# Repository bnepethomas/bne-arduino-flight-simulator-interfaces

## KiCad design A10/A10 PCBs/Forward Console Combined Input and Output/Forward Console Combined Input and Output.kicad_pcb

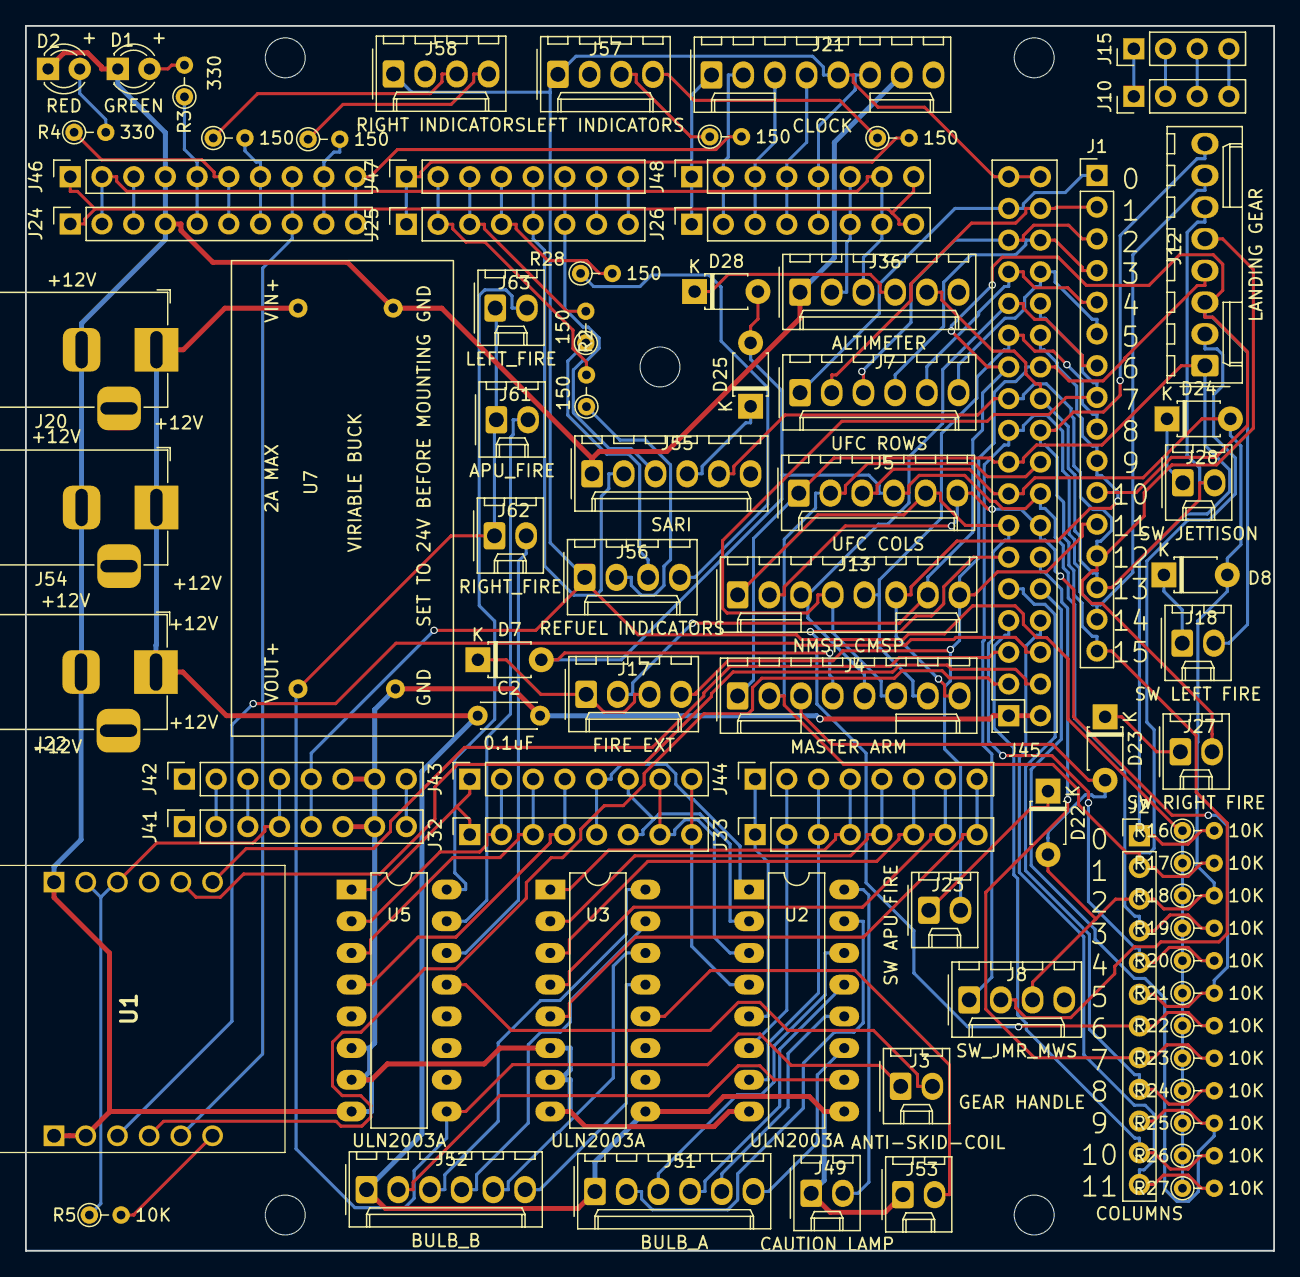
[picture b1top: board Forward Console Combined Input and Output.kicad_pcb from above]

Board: 2 copper layers, 100.0 x 98.1 mm, 87 parts (0 on the bottom side), 116 nets.

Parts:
C2: 0.1uF; C_Disc_D4.3mm_W1.9mm_P5.00mm
D1: GREEN; LED_D3.0mm
D2: RED; LED_D3.0mm
D7, D8, D22, D23, D24, D25, D28: D; D_T-1_P5.08mm_Horizontal
H1, H2, H3, H4: MountingHole; MountingHole_3.2mm
J1: ROWS; PinHeader_1x16_P2.54mm_Vertical
J2: COLUMNS; PinHeader_1x12_P2.54mm_Vertical
J3: GEAR HANDLE; Molex_KK-254_AE-6410-02A_1x02_P2.54mm_Vertical
J4: MASTER ARM; Molex_KK-254_AE-6410-08A_1x08_P2.54mm_Vertical
J5: UFC COLS; Molex_KK-254_AE-6410-06A_1x06_P2.54mm_Vertical
J7: UFC ROWS; Molex_KK-254_AE-6410-06A_1x06_P2.54mm_Vertical
J8: SW_JMR_MWS; Molex_KK-254_AE-6410-04A_1x04_P2.54mm_Vertical
J10, J15: PATCH; PinHeader_1x04_P2.54mm_Vertical
J12: LANDING GEAR; Molex_KK-254_AE-6410-08A_1x08_P2.54mm_Vertical
J13: NMSP CMSP; Molex_KK-254_AE-6410-08A_1x08_P2.54mm_Vertical
J17: FIRE EXT; Molex_KK-254_AE-6410-04A_1x04_P2.54mm_Vertical
J18: SW LEFT FIRE; Molex_KK-254_AE-6410-02A_1x02_P2.54mm_Vertical
J20: 12Vout; BarrelJack_Horizontal
J21: CLOCK; Molex_KK-254_AE-6410-08A_1x08_P2.54mm_Vertical
J22: 12VIN; BarrelJack_Horizontal
J23: SW APU FIRE; Molex_KK-254_AE-6410-02A_1x02_P2.54mm_Vertical
J24, J46: PWM; PinSocket_1x10_P2.54mm_Vertical
J25, J47: PWM; PinSocket_1x08_P2.54mm_Vertical
J26, J48: Communication; PinSocket_1x08_P2.54mm_Vertical
J27: SW RIGHT FIRE; Molex_KK-254_AE-6410-02A_1x02_P2.54mm_Vertical
J28: SW JETTISON; Molex_KK-254_AE-6410-02A_1x02_P2.54mm_Vertical
J32, J33, J43, J44: Analog; PinSocket_1x08_P2.54mm_Vertical
J36: ALTIMETER; Molex_KK-254_AE-6410-06A_1x06_P2.54mm_Vertical
J41, J42: Power; PinSocket_1x08_P2.54mm_Vertical
J45: Digital; PinSocket_2x18_P2.54mm_Vertical
J49: CAUTION LAMP; Molex_KK-254_AE-6410-02A_1x02_P2.54mm_Vertical
J51: BULB_A; Molex_KK-254_AE-6410-06A_1x06_P2.54mm_Vertical
J52: BULB_B; Molex_KK-254_AE-6410-06A_1x06_P2.54mm_Vertical
J53: ANTI-SKID-COIL; Molex_KK-254_AE-6410-02A_1x02_P2.54mm_Vertical
J54: 12VOUT; BarrelJack_Horizontal
J55: SARI; Molex_KK-254_AE-6410-06A_1x06_P2.54mm_Vertical
J56: REFUEL INDICATORS; Molex_KK-254_AE-6410-04A_1x04_P2.54mm_Vertical
J57: LEFT INDICATORS; Molex_KK-254_AE-6410-04A_1x04_P2.54mm_Vertical
J58: RIGHT INDICATORS; Molex_KK-254_AE-6410-04A_1x04_P2.54mm_Vertical
J61: APU_FIRE; Molex_KK-254_AE-6410-02A_1x02_P2.54mm_Vertical
J62: RIGHT_FIRE; Molex_KK-254_AE-6410-02A_1x02_P2.54mm_Vertical
J63: LEFT_FIRE; Molex_KK-254_AE-6410-02A_1x02_P2.54mm_Vertical
MH1: MountingHole_3.2mm
R1, R2, R28, R29, R30, R31, R32: 150; R_Axial_DIN0204_L3.6mm_D1.6mm_P2.54mm_Vertical
R3, R4: 330; R_Axial_DIN0204_L3.6mm_D1.6mm_P2.54mm_Vertical
R5, R16, R17, R18, R19, R20, R21, R22, R23, R24, R25, R26, R27: 10K; R_Axial_DIN0204_L3.6mm_D1.6mm_P2.54mm_Vertical
U1: USR-ES1; USRES1
U2, U3, U5: ULN2003A; DIP-16_W7.62mm_LongPads
U7: VIRIABLE BUCK; VARIABLE_BUCK

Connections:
+3V3: J41.4, J42.4, R5.1, U1.B2 (3V3_1), U1.B3 (3V3_2)
+5V: J21.5, J41.5, J42.5, J45.35, J45.36, J56.1, J57.1, J58.1, R16.1, R17.1, R18.1, R19.1, R20.1, R21.1, R22.1, R23.1, R24.1, R25.1, R26.1, R27.1
+12V: C2.1, J20.1, J22.1, J49.1, J51.1, J52.1, J53.1, J54.1, U2.9 (COM), U3.9 (COM), U7.1 (VIN)
+24V: J3.1, J61.1, J62.1, J63.1, U5.9 (COM), U7.4 (24V_OUT)
/*12: J24.6, J46.6, R4.1
/*13: J24.5, J46.5, R3.1
/AREF: J24.3, J46.3
/COIL AND LAMP DRIVERS/ANCHR: J52.4, U3.15 (O2)
/COIL AND LAMP DRIVERS/B_APU_FIRE: J61.2, U5.15 (O2)
/COIL AND LAMP DRIVERS/B_GEAR HANDLE: J3.2, U5.13 (O4)
/COIL AND LAMP DRIVERS/B_LEFT_FIRE: J63.2, U5.16 (O1)
/COIL AND LAMP DRIVERS/B_RIGHT_FIRE: J62.2, U5.14 (O3)
/COIL AND LAMP DRIVERS/CAUTION_LAMP-: J49.2, U2.16 (O1)
/COIL AND LAMP DRIVERS/COIL_ANTI_SKID: J53.2, U3.12 (O5)
/COIL AND LAMP DRIVERS/EGI: J51.6, U2.11 (O6)
/COIL AND LAMP DRIVERS/HARS: J51.5, U2.12 (O5)
/COIL AND LAMP DRIVERS/ILS: J52.6, U3.13 (O4)
/COIL AND LAMP DRIVERS/MISSLE LAUNCH: J51.4, U2.13 (O4)
/COIL AND LAMP DRIVERS/PRI: J51.2, U2.15 (O2)
/COIL AND LAMP DRIVERS/SEP: J51.3, U2.14 (O3)
/COIL AND LAMP DRIVERS/STR PT: J52.3, U3.16 (O1)
/COIL AND LAMP DRIVERS/TCN: J52.5, U3.14 (O3)
/COIL AND LAMP DRIVERS/TISL: J52.2, U2.10 (O7)
/IOREF: J41.2, J42.2
/~RESET: J41.3, J42.3
A0 D54: J32.1, J43.1, U5.1 (I1)
A1 D55: J32.2, J43.2, U5.2 (I2)
A2 D56: J32.3, J43.3, U5.3 (I3)
A3 D57: J32.4, J43.4, U5.4 (I4)
A4 D58: J32.5, J43.5, U2.1 (I1)
A5 D59: J32.6, J43.6, U2.2 (I2)
A6 D60: J32.7, J43.7, U2.3 (I3)
A7 D61: J32.8, J43.8, U2.4 (I4)
A8 D62: J33.1, J44.1, U2.5 (I5)
A9 D63: J33.2, J44.2, U2.6 (I6)
A10 D64: J33.3, J44.3, U2.7 (I7)
A11 D65: J33.4, J44.4, U3.1 (I1)
A12 D66: J33.5, J44.5, U3.2 (I2)
A13 D67: J33.6, J44.6, U3.3 (I3)
A14 D68: J33.7, J44.7, U3.4 (I4)
A15 D69: J33.8, J44.8, U3.5 (I5)
D0: J25.8, J47.8
D1: J25.7, J47.7
D2: J25.6, J47.6, J55.3
D3: J25.5, J47.5, J55.2
D4: J25.4, J47.4, R28.2
D5: J25.3, J47.3, R2.2
D6: J25.2, J47.2, R1.2
D7: J25.1, J47.1, R30.2
D8: J24.10, J46.10, R29.2
D9: J24.9, J46.9, R32.2
D11: J24.7, J46.7, R31.2
D14: J21.1, J26.1, J48.1
D15: J21.2, J26.2, J48.2
D16: J21.3, J26.3, J48.3
D17: J21.4, J26.4, J48.4
D18: J21.6, J26.5, J48.5
D19: J26.6, J36.2, J48.6
D20 SDA: J24.2, J26.7, J36.3, J46.2, J48.7
D21 SCL: J24.1, J26.8, J46.1, J48.8
D22: J1.1, J7.1, J45.33
D23: J1.2, J7.2, J45.34
D24: J1.3, J7.3, J45.31
D25: J1.4, J7.4, J45.32
D26: J1.5, J7.5, J45.29
D27: J1.6, J7.6, J45.30
D28: J1.7, J4.5, J13.3, J45.27
D29: J1.8, J4.6, J13.4, J45.28
D30: J1.9, J4.7, J13.5, J45.25
D31: J1.10, J4.8, J13.6, J45.26
D32: J1.11, J12.3, J13.7, J17.2, J18.2, J45.23
D33: J1.12, J12.4, J13.8, J17.4, J23.2, J45.24
D34: J1.13, J12.5, J27.2, J45.21, J55.5
D35: J1.14, J12.6, J28.2, J36.5, J45.22
D36: J1.15, J8.1, J12.7, J45.19
D37: J1.16, J8.2, J12.8, J45.20
D38: J2.1, J4.1, J5.1, J12.1, J45.17, R16.2
D39: J2.2, J4.2, J5.2, J12.2, J45.18, R17.2
D40: D8.2 (A), D22.2 (A), D23.2 (A), D24.2 (A), J2.3, J4.3, J5.3, J8.3, J45.15, R18.2
D41: D7.2 (A), D25.2 (A), D28.2 (A), J2.4, J4.4, J5.4, J45.16, R19.2
D42: J2.5, J5.5, J13.1, J45.13, R20.2
D43: J2.6, J5.6, J13.2, J45.14, R21.2
D44: J2.7, J45.11, R22.2
D45: J2.8, J45.12, R23.2
D46: J2.9, J45.9, R24.2
D47: J2.10, J45.10, R25.2
D48: J2.11, J45.7, R26.2
D49: J2.12, J45.8, R27.2
ES1_RST: J45.4, U1.B5 (RST)
GND: C2.2, D1.1 (K), D2.1 (K), J20.2, J21.7, J22.2, J24.4, J36.1, J41.6, J41.7, J42.6, J42.7, J45.1, J45.2, J46.4, J54.2, J55.1, U1.A1 (GND_1), U1.A2 (GND_2), U1.B1 (GND_3), U2.8 (GND), U3.6 (I6), U3.7 (I7), U3.8 (GND), U5.6 (I6), U5.7 (I7), U5.8 (GND), U7.2 (GND), U7.3 (GND)
MISO: J45.5, U1.B6 (MISO)
MOSI: J45.6, U1.A3 (MOSI)
unnamed: D1.2 (A), R3.2
unnamed: D2.2 (A), R4.2
unnamed: D7.1 (K), J17.1, J17.3
unnamed: D8.1 (K), J18.1
unnamed: D22.1 (K), J23.1
unnamed: D23.1 (K), J27.1
unnamed: D24.1 (K), J28.1
unnamed: D25.1 (K), J55.4
unnamed: D28.1 (K), J36.4
unnamed: J10.1, J15.1
unnamed: J10.2, J15.2
unnamed: J10.3, J15.3
unnamed: J10.4, J15.4
unnamed: J56.2, R1.1
unnamed: J56.3, R2.1
unnamed: J56.4, R28.1
unnamed: J57.3, R29.1
unnamed: J57.4, R30.1
unnamed: J58.3, R31.1
unnamed: J58.4, R32.1
unnamed: R5.2, U1.A6 (INT)
SCLK: J45.3, U1.A4 (SCLK)
SS: J24.8, J46.8, U1.A5 (CS)
VCC: J41.8, J42.8

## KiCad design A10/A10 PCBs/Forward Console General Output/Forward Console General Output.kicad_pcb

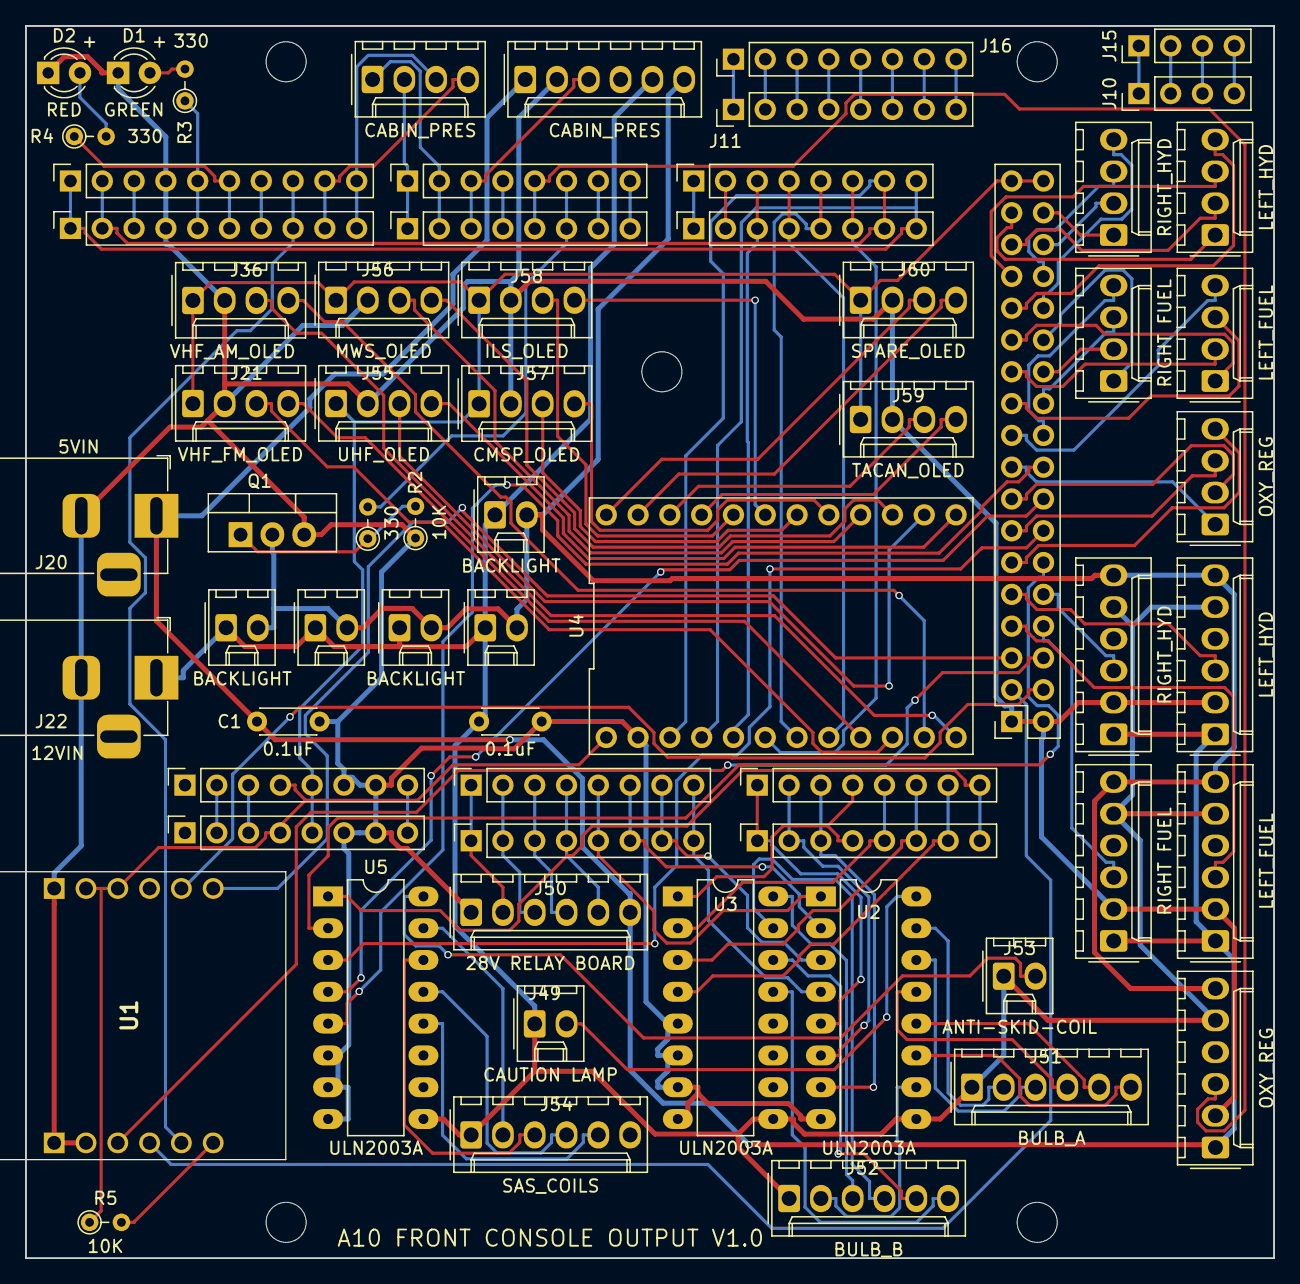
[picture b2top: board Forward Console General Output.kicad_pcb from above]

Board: 2 copper layers, 99.7 x 98.4 mm, 70 parts (0 on the bottom side), 128 nets.

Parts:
C1, C2: 0.1uF; C_Disc_D4.3mm_W1.9mm_P5.00mm
D1: GREEN; LED_D3.0mm
D2: RED; LED_D3.0mm
H1, H2, H3, H4: MountingHole; MountingHole_3.2mm
J3, J6, J9, J14, J19: BACKLIGHT; Molex_KK-254_AE-6410-02A_1x02_P2.54mm_Vertical
J10, J15: PATCH; PinHeader_1x04_P2.54mm_Vertical
J11, J16: PATCH; PinHeader_1x08_P2.54mm_Vertical
J20: 5VIN; BarrelJack_Horizontal
J21: VHF_FM_OLED; Molex_KK-254_AE-6410-04A_1x04_P2.54mm_Vertical
J22: 12VIN; BarrelJack_Horizontal
J23: CABIN_PRES; Molex_KK-254_AE-6410-06A_1x06_P2.54mm_Vertical
J24, J46: PWM; PinSocket_1x10_P2.54mm_Vertical
J25, J47: PWM; PinSocket_1x08_P2.54mm_Vertical
J26, J48: Communication; PinSocket_1x08_P2.54mm_Vertical
J27: OXY_REG; Molex_KK-254_AE-6410-06A_1x06_P2.54mm_Vertical
J28: RIGHT FUEL; Molex_KK-254_AE-6410-06A_1x06_P2.54mm_Vertical
J29: LEFT_FUEL; Molex_KK-254_AE-6410-06A_1x06_P2.54mm_Vertical
J30: RIGHT_HYD; Molex_KK-254_AE-6410-06A_1x06_P2.54mm_Vertical
J31: LEFT_HYD; Molex_KK-254_AE-6410-06A_1x06_P2.54mm_Vertical
J32, J33, J43, J44: Analog; PinSocket_1x08_P2.54mm_Vertical
J34: CABIN_PRES; Molex_KK-254_AE-6410-04A_1x04_P2.54mm_Vertical
J35: OXY_REG; Molex_KK-254_AE-6410-04A_1x04_P2.54mm_Vertical
J36: VHF_AM_OLED; Molex_KK-254_AE-6410-04A_1x04_P2.54mm_Vertical
J37: RIGHT_HYD; Molex_KK-254_AE-6410-04A_1x04_P2.54mm_Vertical
J38: LEFT_FUEL; Molex_KK-254_AE-6410-04A_1x04_P2.54mm_Vertical
J39: RIGHT FUEL; Molex_KK-254_AE-6410-04A_1x04_P2.54mm_Vertical
J40: LEFT_HYD; Molex_KK-254_AE-6410-04A_1x04_P2.54mm_Vertical
J41, J42: Power; PinSocket_1x08_P2.54mm_Vertical
J45: Digital; PinSocket_2x18_P2.54mm_Vertical
J49: CAUTION LAMP; Molex_KK-254_AE-6410-02A_1x02_P2.54mm_Vertical
J50: 28V RELAY BOARD; Molex_KK-254_AE-6410-06A_1x06_P2.54mm_Vertical
J51: BULB_A; Molex_KK-254_AE-6410-06A_1x06_P2.54mm_Vertical
J52: BULB_B; Molex_KK-254_AE-6410-06A_1x06_P2.54mm_Vertical
J53: ANTI-SKID-COIL; Molex_KK-254_AE-6410-02A_1x02_P2.54mm_Vertical
J54: SAS_COILS; Molex_KK-254_AE-6410-06A_1x06_P2.54mm_Vertical
J55: UHF_OLED; Molex_KK-254_AE-6410-04A_1x04_P2.54mm_Vertical
J56: MWS_OLED; Molex_KK-254_AE-6410-04A_1x04_P2.54mm_Vertical
J57: CMSP_OLED; Molex_KK-254_AE-6410-04A_1x04_P2.54mm_Vertical
J58: ILS_OLED; Molex_KK-254_AE-6410-04A_1x04_P2.54mm_Vertical
J59: TACAN_OLED; Molex_KK-254_AE-6410-04A_1x04_P2.54mm_Vertical
J60: SPARE_OLED; Molex_KK-254_AE-6410-04A_1x04_P2.54mm_Vertical
MH1: MountingHole_3.2mm
Q1: IRF1405PBF; TO-220-3_Vertical
R1, R3, R4: 330; R_Axial_DIN0204_L3.6mm_D1.6mm_P2.54mm_Vertical
R2, R5: 10K; R_Axial_DIN0204_L3.6mm_D1.6mm_P2.54mm_Vertical
U1: USR-ES1; USRES1
U2, U3, U5: ULN2003A; DIP-16_W7.62mm_LongPads
U4: TCA9548APWR; DIP-24_TCA9548A

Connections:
+3V3: J41.4, J42.4, R5.1, U1.B2 (3V3_1), U1.B3 (3V3_2), U4.1 (VCC)
+5V: J21.1, J36.1, J41.5, J42.5, J45.35, J45.36, J55.1, J56.1, J57.1, J58.1, J59.1, J60.1
+5VD: C1.1, J20.1, J23.1, J27.1, J28.1, J29.1, J30.1, J31.1, J50.6
+12V: C2.1, J3.1, J6.1, J9.1, J14.1, J19.1, J22.1, J23.5, J27.5, J28.5, J29.5, J30.5, J31.5, J49.1, J51.1, J52.1, J53.1, J54.1, U2.9 (COM), U3.9 (COM), U5.9 (COM)
/22: J40.1, J45.33
/23: J37.1, J45.34
/24: J40.2, J45.31
/25: J37.2, J45.32
/26: J40.3, J45.29
/27: J37.3, J45.30
/28: J40.4, J45.27
/29: J37.4, J45.28
/30: J38.1, J45.25
/31: J39.1, J45.26
/32: J38.2, J45.23
/33: J39.2, J45.24
/34: J38.3, J45.21
/35: J39.3, J45.22
/36: J38.4, J45.19
/37: J39.4, J45.20
/38: J35.1, J45.17
/40: J35.2, J45.15
/42: J35.3, J45.13
/47: J30.3, J45.10
/48: J29.3, J45.7
/49: J28.3, J45.8
/*2: J25.6, J47.6, R1.2
/*3: J25.5, J27.3, J47.5
/*4: J25.4, J47.4
/*5: J23.3, J25.3, J47.3
/*6: J25.2, J34.1, J47.2
/*7: J25.1, J34.2, J47.1
/*8: J24.10, J34.3, J46.10
/*9: J24.9, J34.4, J46.9
/*11: J24.7, J46.7
/*12: J24.6, J46.6, R4.1
/*13: J24.5, J46.5, R3.1
/*44: J35.4, J45.11
/*46: J31.3, J45.9
/A0: J32.1, J43.1, J50.2
/A1: J32.2, J43.2, J50.3
/A2: J32.3, J43.3, J50.4
/A3: J32.4, J43.4, J50.5
/AREF: J24.3, J46.3
/BACKLIGHT_-V: J3.2, J6.2, J9.2, J14.2, J19.2, J23.6, J27.6, J28.6, J29.6, J30.6, J31.6, Q1.2 (D)
/COIL AND LAMP DRIVERS/ANCHR: J52.4, U3.15 (O2)
/COIL AND LAMP DRIVERS/CAUTION_LAMP-: J49.2, U2.16 (O1)
/COIL AND LAMP DRIVERS/COIL_ANTI_SKID: J53.2, U5.16 (O1)
/COIL AND LAMP DRIVERS/COIL_L_PITCH: J54.4, U5.13 (O4)
/COIL AND LAMP DRIVERS/COIL_L_YAW: J54.2, U5.15 (O2)
/COIL AND LAMP DRIVERS/COIL_R_PITCH: J54.5, U5.12 (O5)
/COIL AND LAMP DRIVERS/COIL_R_YAW: J54.3, U5.14 (O3)
/COIL AND LAMP DRIVERS/EGI: J51.6, U2.11 (O6)
/COIL AND LAMP DRIVERS/HARS: J51.5, U2.12 (O5)
/COIL AND LAMP DRIVERS/ILS: J52.6, U3.13 (O4)
/COIL AND LAMP DRIVERS/MISSLE LAUNCH: J51.4, U2.13 (O4)
/COIL AND LAMP DRIVERS/PRI: J51.2, U2.15 (O2)
/COIL AND LAMP DRIVERS/SEP: J51.3, U2.14 (O3)
/COIL AND LAMP DRIVERS/STR PT: J52.3, U3.16 (O1)
/COIL AND LAMP DRIVERS/TCN: J52.5, U3.14 (O3)
/COIL AND LAMP DRIVERS/TISL: J52.2, U2.10 (O7)
/I2C_SEL_A0: J26.4, J48.4, U4.8 (A2)
/I2C_SEL_A1: J26.5, J48.5, U4.7 (A1)
/I2C_SEL_A2: J26.6, J48.6, U4.6 (A0)
/I2C_SEL_RESET: J26.3, J48.3, U4.5 (~RESET)
/IOREF: J41.2, J42.2
/RX0/0: J25.8, J47.8
/RX3/15: J26.2, J48.2
/SC0: J21.3, U4.10 (SC0)
/SC1: J36.3, U4.12 (SC1)
/SC2: J55.3, U4.14 (SC2)
/SC3: J56.3, U4.16 (SC3)
/SC4: J57.3, U4.18 (SC4)
/SC5: J58.3, U4.20 (SC5)
/SC6: J59.3, U4.22 (SC6)
/SC7: J60.3, U4.24 (SC7)
/SCL: J24.1, J26.8, J46.1, J48.8, U4.4 (SCL)
/SD0: J21.4, U4.9 (SD0)
/SD1: J36.4, U4.11 (SD1)
/SD2: J55.4, U4.13 (SD2)
/SD3: J56.4, U4.15 (SD3)
/SD4: J57.4, U4.17 (SD4)
/SD5: J58.4, U4.19 (SD5)
/SD6: J59.4, U4.21 (SD6)
/SD7: J60.4, U4.23 (SD7)
/SDA: J24.2, J26.7, J46.2, J48.7, U4.3 (SDA)
/TX0/1: J25.7, J47.7
/TX3/14: J26.1, J48.1
/~RESET: J41.3, J42.3
ES1_RST: J45.4, U1.B5 (RST)
GND: C1.2, C2.2, D1.1 (K), D2.1 (K), J20.2, J21.2, J22.2, J23.2, J24.4, J27.2, J28.2, J29.2, J30.2, J31.2, J36.2, J41.6, J41.7, J42.6, J42.7, J45.1, J45.2, J46.4, J50.1, J55.2, J56.2, J57.2, J58.2, J59.2, J60.2, Q1.3 (S), R2.1, U1.A1 (GND_1), U1.A2 (GND_2), U1.B1 (GND_3), U2.8 (GND), U3.5 (I5), U3.6 (I6), U3.7 (I7), U3.8 (GND), U4.2 (GND), U5.6 (I6), U5.7 (I7), U5.8 (GND)
MISO: J45.5, U1.B6 (MISO)
MOSI: J45.6, U1.A3 (MOSI)
unnamed: D1.2 (A), R3.2
unnamed: D2.2 (A), R4.2
unnamed: J10.1, J15.1
unnamed: J10.2, J15.2
unnamed: J10.3, J15.3
unnamed: J10.4, J15.4
unnamed: J11.1, J16.1
unnamed: J11.2, J16.2
unnamed: J11.3, J16.3
unnamed: J11.4, J16.4
unnamed: J11.5, J16.5
unnamed: J11.6, J16.6
unnamed: J11.7, J16.7
unnamed: J11.8, J16.8
unnamed: Q1.1 (G), R1.1, R2.2
unnamed: R5.2, U1.A6 (INT)
O_ANCHR_LAMP: J33.5, J44.5, U3.2 (I2)
O_ANTI_SKID: J33.8, J44.8, U5.1 (I1)
O_CAUTION_LAMP-: J32.5, J43.5, U2.1 (I1)
O_COIL_L_PITCH: J45.16, U5.4 (I4)
O_COIL_L_YAW: J45.12, U5.2 (I2)
O_COIL_R_PITCH: J45.18, U5.5 (I5)
O_COIL_R_YAW: J45.14, U5.3 (I3)
O_EGI_LAMP: J33.2, J44.2, U2.6 (I6)
O_HARS_LAMP: J33.1, J44.1, U2.5 (I5)
O_ILS_LAMP: J33.7, J44.7, U3.4 (I4)
O_MISSILE_LAMP: J32.8, J43.8, U2.4 (I4)
O_PRI_LAMP: J32.6, J43.6, U2.2 (I2)
O_SEP_LAMP: J32.7, J43.7, U2.3 (I3)
O_STR_PT_LAMP: J33.4, J44.4, U3.1 (I1)
O_TCN_LAMP: J33.6, J44.6, U3.3 (I3)
O_TISL_LAMP: J33.3, J44.3, U2.7 (I7)
SCLK: J45.3, U1.A4 (SCLK)
SS: J24.8, J46.8, U1.A5 (CS)
VCC: J41.8, J42.8

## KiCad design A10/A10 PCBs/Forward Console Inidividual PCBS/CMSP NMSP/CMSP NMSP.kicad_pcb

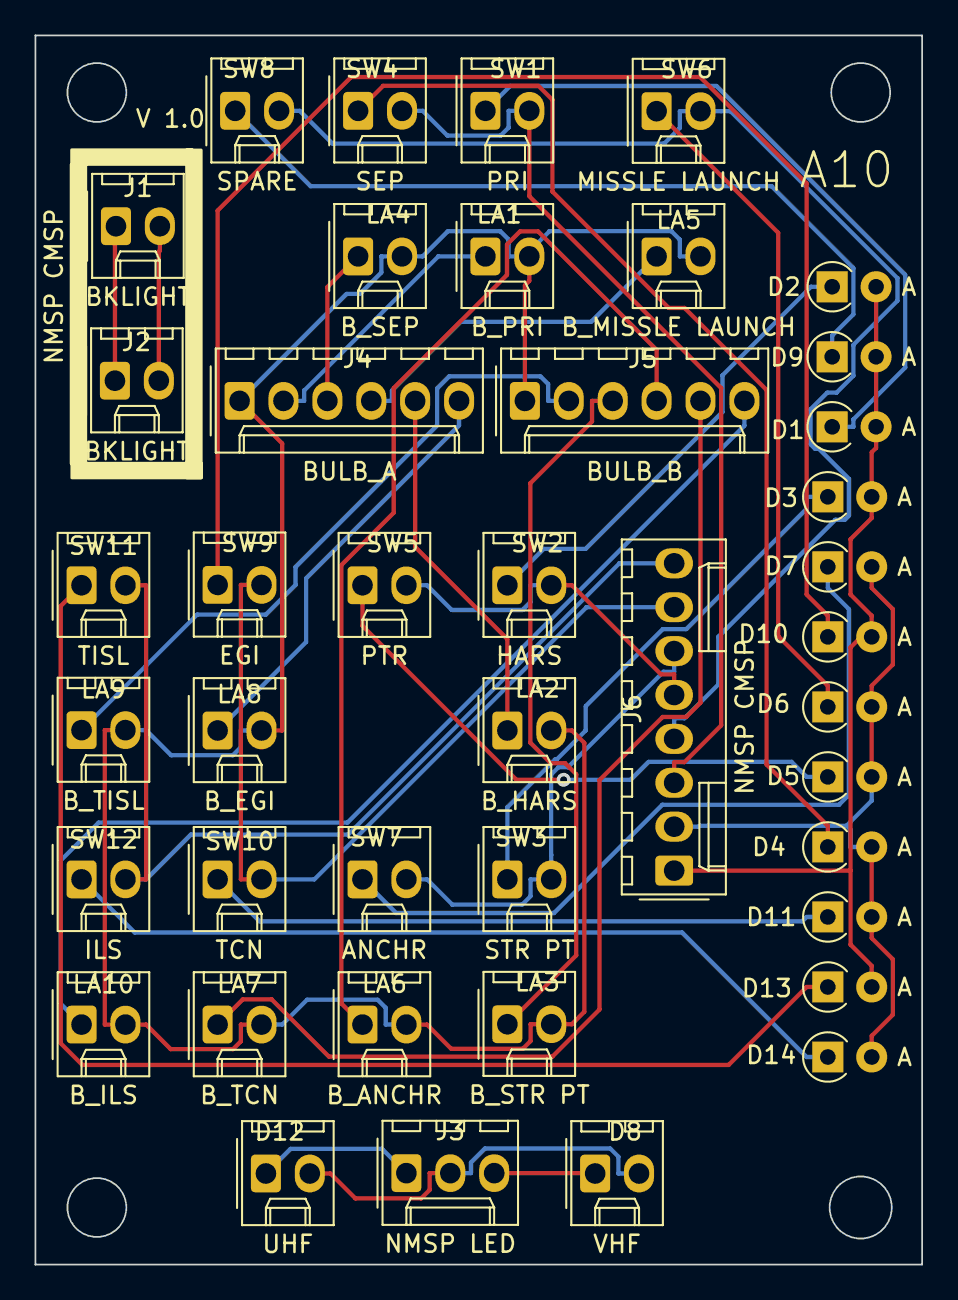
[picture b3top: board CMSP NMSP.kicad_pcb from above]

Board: 2 copper layers, 51.3 x 71.1 mm, 42 parts (0 on the bottom side), 36 nets.

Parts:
D1, D2, D3, D4, D5, D6, D7, D9, D10, D11, D13, D14: D; D_A-405_P2.54mm_Vertical_AnodeUp
D8: VHF; Molex_KK-254_AE-6410-02A_1x02_P2.54mm_Vertical
D12: UHF; Molex_KK-254_AE-6410-02A_1x02_P2.54mm_Vertical
J1, J2: BKLIGHT; Molex_KK-254_AE-6410-02A_1x02_P2.54mm_Vertical
J3: NMSP LED; Molex_KK-254_AE-6410-03A_1x03_P2.54mm_Vertical
J4: BULB_A; Molex_KK-254_AE-6410-06A_1x06_P2.54mm_Vertical
J5: BULB_B; Molex_KK-254_AE-6410-06A_1x06_P2.54mm_Vertical
J6: NMSP CMSP; Molex_KK-254_AE-6410-08A_1x08_P2.54mm_Vertical
LA1: B_PRI; Molex_KK-254_AE-6410-02A_1x02_P2.54mm_Vertical
LA2: B_HARS; Molex_KK-254_AE-6410-02A_1x02_P2.54mm_Vertical
LA3: B_STR PT; Molex_KK-254_AE-6410-02A_1x02_P2.54mm_Vertical
LA4: B_SEP; Molex_KK-254_AE-6410-02A_1x02_P2.54mm_Vertical
LA5: B_MISSLE LAUNCH; Molex_KK-254_AE-6410-02A_1x02_P2.54mm_Vertical
LA6: B_ANCHR; Molex_KK-254_AE-6410-02A_1x02_P2.54mm_Vertical
LA7: B_TCN; Molex_KK-254_AE-6410-02A_1x02_P2.54mm_Vertical
LA8: B_EGI; Molex_KK-254_AE-6410-02A_1x02_P2.54mm_Vertical
LA9: B_TISL; Molex_KK-254_AE-6410-02A_1x02_P2.54mm_Vertical
LA10: B_ILS; Molex_KK-254_AE-6410-02A_1x02_P2.54mm_Vertical
SW1: PRI; Molex_KK-254_AE-6410-02A_1x02_P2.54mm_Vertical
SW2: HARS; Molex_KK-254_AE-6410-02A_1x02_P2.54mm_Vertical
SW3: STR PT; Molex_KK-254_AE-6410-02A_1x02_P2.54mm_Vertical
SW4: SEP; Molex_KK-254_AE-6410-02A_1x02_P2.54mm_Vertical
SW5: PTR; Molex_KK-254_AE-6410-02A_1x02_P2.54mm_Vertical
SW6: MISSLE LAUNCH; Molex_KK-254_AE-6410-02A_1x02_P2.54mm_Vertical
SW7: ANCHR; Molex_KK-254_AE-6410-02A_1x02_P2.54mm_Vertical
SW8: SPARE; Molex_KK-254_AE-6410-02A_1x02_P2.54mm_Vertical
SW9: EGI; Molex_KK-254_AE-6410-02A_1x02_P2.54mm_Vertical
SW10: TCN; Molex_KK-254_AE-6410-02A_1x02_P2.54mm_Vertical
SW11: TISL; Molex_KK-254_AE-6410-02A_1x02_P2.54mm_Vertical
SW12: ILS; Molex_KK-254_AE-6410-02A_1x02_P2.54mm_Vertical

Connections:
/+12V: J4.1, J5.1, LA1.2 (+), LA2.2 (+), LA3.2 (+), LA4.2 (+), LA5.2 (+), LA6.2 (+), LA7.2 (+), LA8.2 (+), LA9.2 (+), LA10.2 (+)
/ANCHR: J5.4, LA6.1 (-)
/COL4: D1.2 (A), D2.2 (A), D3.2 (A), D9.2 (A), D10.2 (A), D13.2 (A), J6.1
/COL5: D4.2 (A), D5.2 (A), D6.2 (A), D7.2 (A), D11.2 (A), D14.2 (A), J6.2
/EGI: J4.6, LA8.1 (-)
/HARS: J4.5, LA2.1 (-)
/ILS: J5.6, LA10.1 (-)
/MISSLE LAUNCH: J4.4, LA5.1 (-)
/PRI: J4.2, LA1.1 (-)
/ROW6: J6.3, SW1.2, SW4.2
/ROW7: J6.4, SW6.2, SW8.2
/ROW8: J6.5, SW2.2, SW5.2 (B)
/ROW9: J6.6, SW3.2, SW7.2
/ROW10: J6.7, SW9.2, SW10.2
/ROW11: J6.8, SW11.2, SW12.2
/SEP: J4.3, LA4.1 (-)
/STR PT: J5.3, LA3.1 (-)
/TCN: J5.5, LA7.1 (-)
/TISL: J5.2, LA9.1 (-)
unnamed: D1.1 (K), SW1.1
unnamed: D2.1 (K), SW2.1
unnamed: D3.1 (K), SW3.1
unnamed: D4.1 (K), SW4.1
unnamed: D5.1 (K), SW5.1 (A)
unnamed: D6.1 (K), SW6.1
unnamed: D7.1 (K), SW7.1
unnamed: D8.1 (K), J3.3
unnamed: D9.1 (K), SW8.1
unnamed: D10.1 (K), SW9.1
unnamed: D11.1 (K), SW10.1
unnamed: D8.2 (A), D12.2 (A), J3.2
unnamed: D12.1 (K), J3.1
unnamed: D13.1 (K), SW11.1
unnamed: D14.1 (K), SW12.1
unnamed: J1.1, J2.1
unnamed: J1.2, J2.2

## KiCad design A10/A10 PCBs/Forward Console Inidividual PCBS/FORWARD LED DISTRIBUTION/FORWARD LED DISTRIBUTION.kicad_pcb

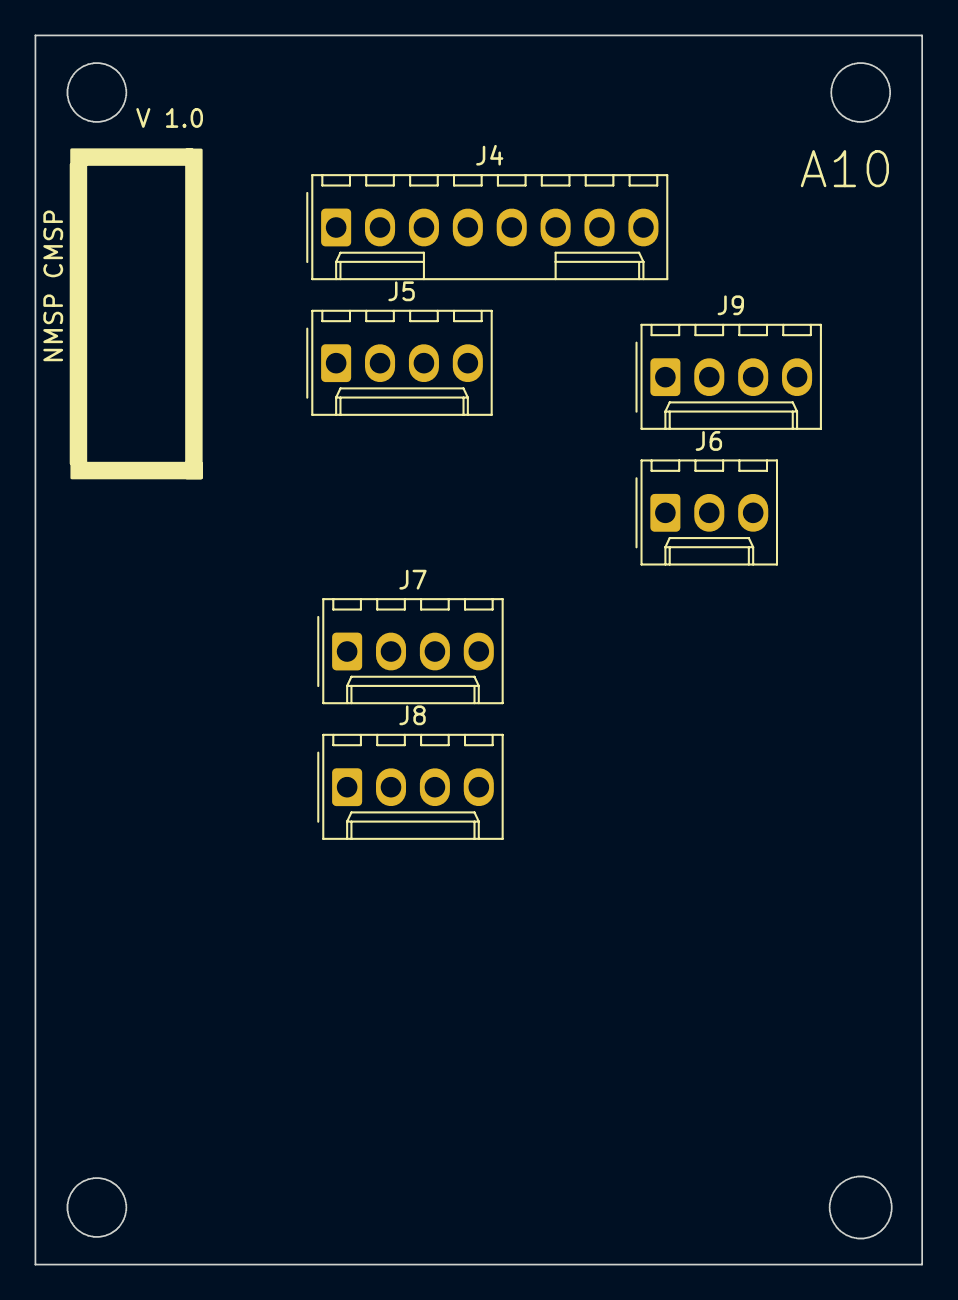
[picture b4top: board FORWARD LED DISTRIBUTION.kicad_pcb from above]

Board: 2 copper layers, 51.3 x 71.1 mm, 6 parts (0 on the bottom side), 10 nets, no tracks yet.

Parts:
J4: FORWARD_SEGEMENTS; Molex_KK-254_AE-6410-08A_1x08_P2.54mm_Vertical
J5: FORWARD_DIGITS; Molex_KK-254_AE-6410-04A_1x04_P2.54mm_Vertical
J6: TAKE OFF TRIM; Molex_KK-254_AE-6410-03A_1x03_P2.54mm_Vertical
J7: LEFT FORWARD LEDS; Molex_KK-254_AE-6410-04A_1x04_P2.54mm_Vertical
J8: RIGHT FORWARD LEDS; Molex_KK-254_AE-6410-04A_1x04_P2.54mm_Vertical
J9: CMSP; Molex_KK-254_AE-6410-04A_1x04_P2.54mm_Vertical

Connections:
/DIG_B4: J5.1, J6.2, J7.1, J9.2
/DIG_B5: J5.2, J7.2
/DIG_B6: J5.3, J8.1
/DIG_B7: J5.4, J8.2
/SEG_A1: J4.1, J6.1
/SEG_B1: J4.2, J6.3
/SEG_C1: J4.3, J7.3, J8.3
/SEG_D1: J4.4, J7.4, J8.4
/SEG_E1: J4.5, J9.1
/SEG_F1: J4.6, J9.3

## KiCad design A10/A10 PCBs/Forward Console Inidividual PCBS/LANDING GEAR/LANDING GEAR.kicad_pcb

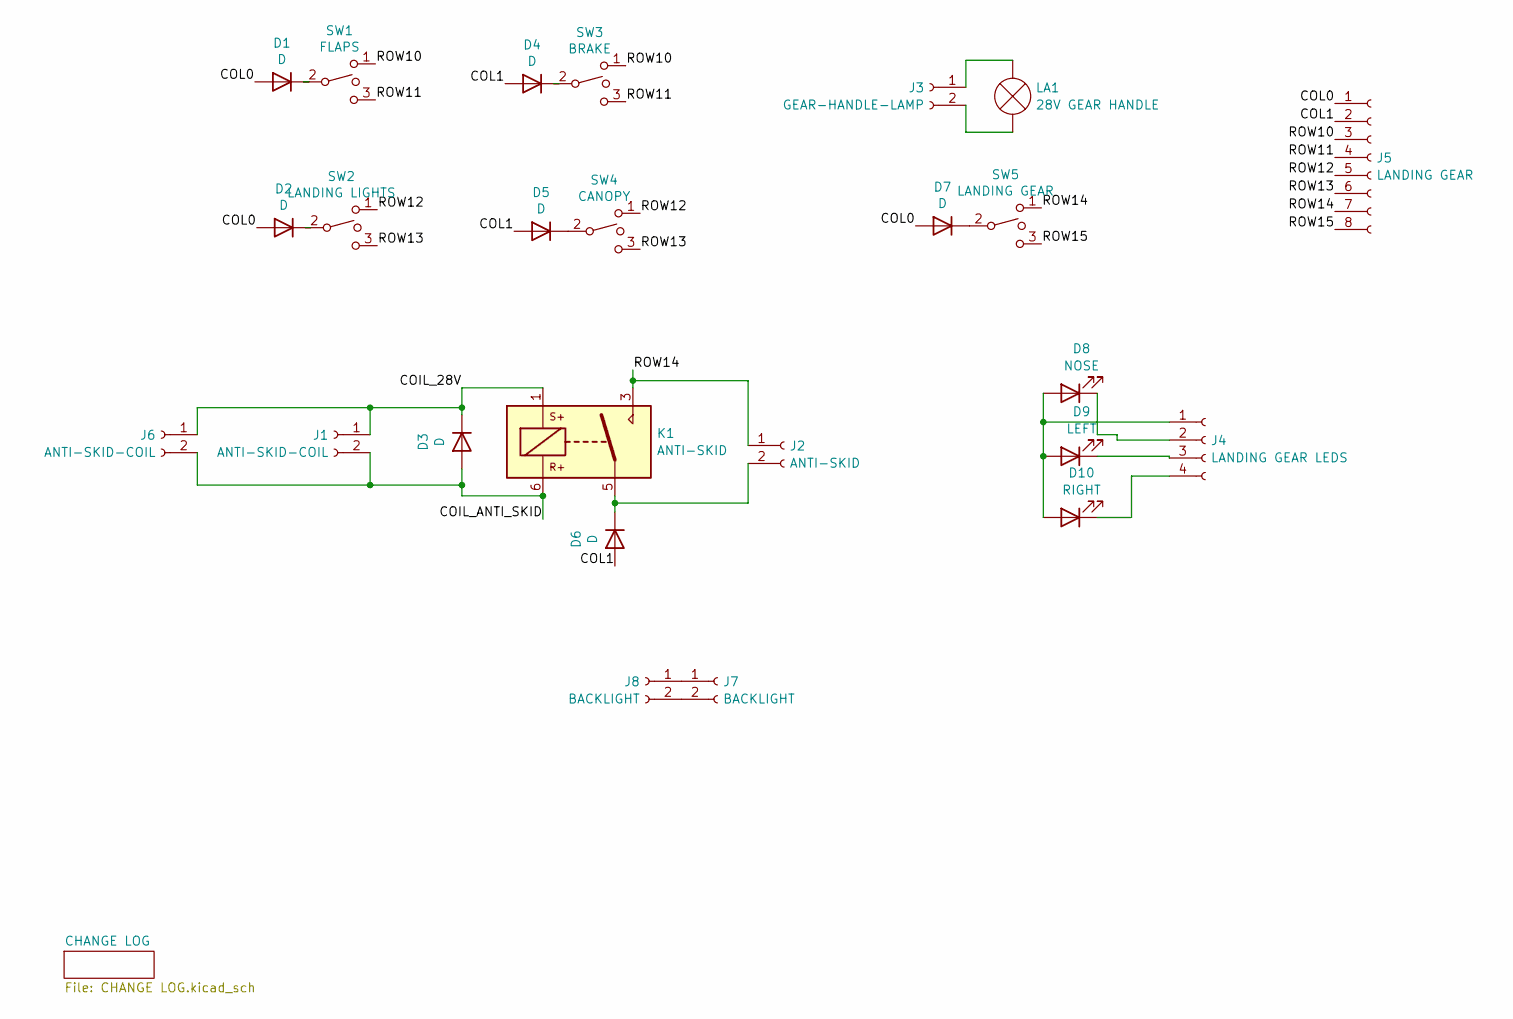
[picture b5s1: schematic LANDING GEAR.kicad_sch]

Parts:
D1, D2, D3, D4, D5, D6, D7: D; D_A-405_P2.54mm_Vertical_AnodeUp
D8: NOSE; Molex_KK-254_AE-6410-02A_1x02_P2.54mm_Vertical
D9: LEFT; Molex_KK-254_AE-6410-02A_1x02_P2.54mm_Vertical
D10: RIGHT; Molex_KK-254_AE-6410-02A_1x02_P2.54mm_Vertical
J1, J6: ANTI-SKID-COIL; Molex_KK-254_AE-6410-02A_1x02_P2.54mm_Vertical
J2: ANTI-SKID; Molex_KK-254_AE-6410-02A_1x02_P2.54mm_Vertical
J3: GEAR-HANDLE-LAMP; Molex_KK-254_AE-6410-02A_1x02_P2.54mm_Vertical
J4: LANDING GEAR LEDS; Molex_KK-254_AE-6410-04A_1x04_P2.54mm_Vertical
J5: LANDING GEAR; Molex_KK-254_AE-6410-08A_1x08_P2.54mm_Vertical
J7, J8: BACKLIGHT; Molex_KK-254_AE-6410-02A_1x02_P2.54mm_Vertical
K1: ANTI-SKID; Relay_1P1T_NO_10x24x18.8mm_Panasonic_ADW11xxxxW_THT
LA1: 28V GEAR HANDLE; Molex_KK-254_AE-6410-02A_1x02_P2.54mm_Vertical
SW1: FLAPS; Molex_KK-254_AE-6410-03A_1x03_P2.54mm_Vertical
SW2: LANDING LIGHTS; Molex_KK-254_AE-6410-03A_1x03_P2.54mm_Vertical
SW3: BRAKE; Molex_KK-254_AE-6410-03A_1x03_P2.54mm_Vertical
SW4: CANOPY; Molex_KK-254_AE-6410-03A_1x03_P2.54mm_Vertical
SW5: LANDING GEAR; Molex_KK-254_AE-6410-03A_1x03_P2.54mm_Vertical

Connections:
/COIL_28V: D3.1 (K), J1.1, J6.1, K1.1
/COIL_ANTI_SKID: D3.2 (A), J1.2, J6.2, K1.6
/COL0: D1.2 (A), D2.2 (A), D7.2 (A), J5.1
/COL1: D4.2 (A), D5.2 (A), D6.2 (A), J5.2
/ROW10: J5.3, SW1.1, SW3.1
/ROW11: J5.4, SW1.3, SW3.3
/ROW12: J5.5, SW2.1, SW4.1
/ROW15: J5.8, SW5.3
unnamed: D1.1 (K), SW1.2
unnamed: D2.1 (K), SW2.2
unnamed: D4.1 (K), SW3.2
unnamed: D5.1 (K), SW4.2
unnamed: D6.1 (K), J2.2, K1.5
unnamed: D7.1 (K), SW5.2
unnamed: D8.1 (K), J4.2
unnamed: D9.1 (K), J4.3
unnamed: D8.2 (A), D9.2 (A), D10.2 (A), J4.1
unnamed: D10.1 (K), J4.4
unnamed: J3.1, LA1.1 (-)
unnamed: J3.2, LA1.2 (+)
unnamed: J7.1, J8.1
unnamed: J7.2, J8.2

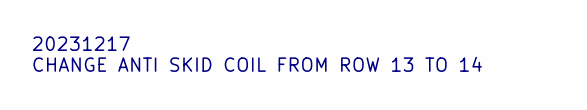
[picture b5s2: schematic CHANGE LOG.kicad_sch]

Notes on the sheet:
20231217 CHANGE ANTI SKID COIL FROM ROW 13 TO 14

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
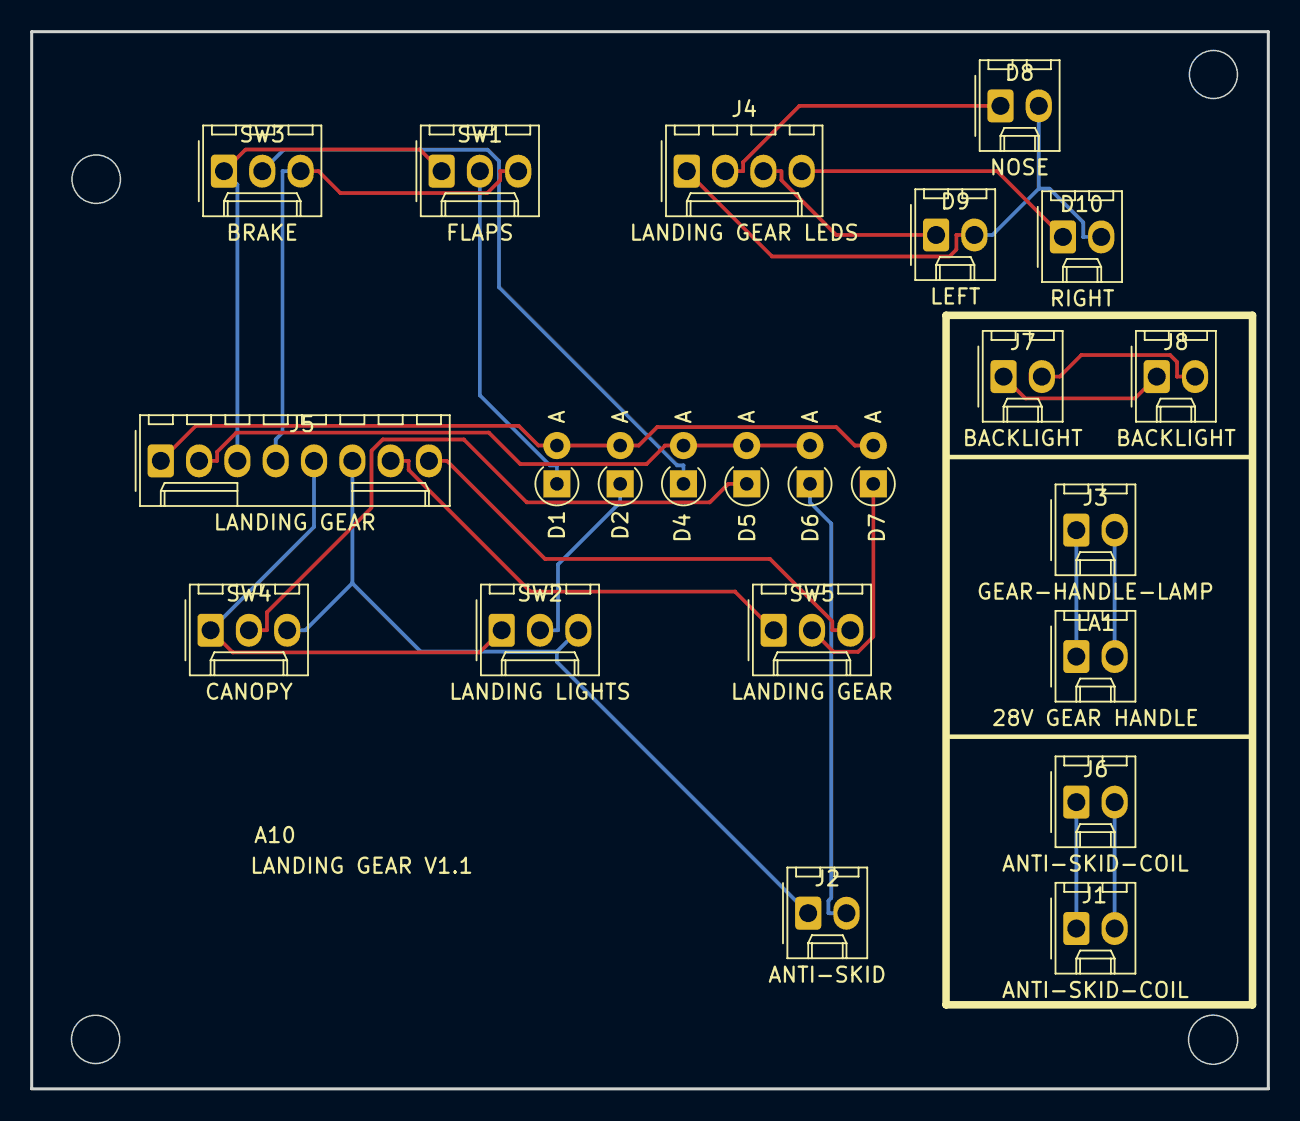
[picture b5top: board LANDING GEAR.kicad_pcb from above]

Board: 2 copper layers, 82.0 x 70.1 mm, 23 parts (0 on the bottom side), 24 nets.
